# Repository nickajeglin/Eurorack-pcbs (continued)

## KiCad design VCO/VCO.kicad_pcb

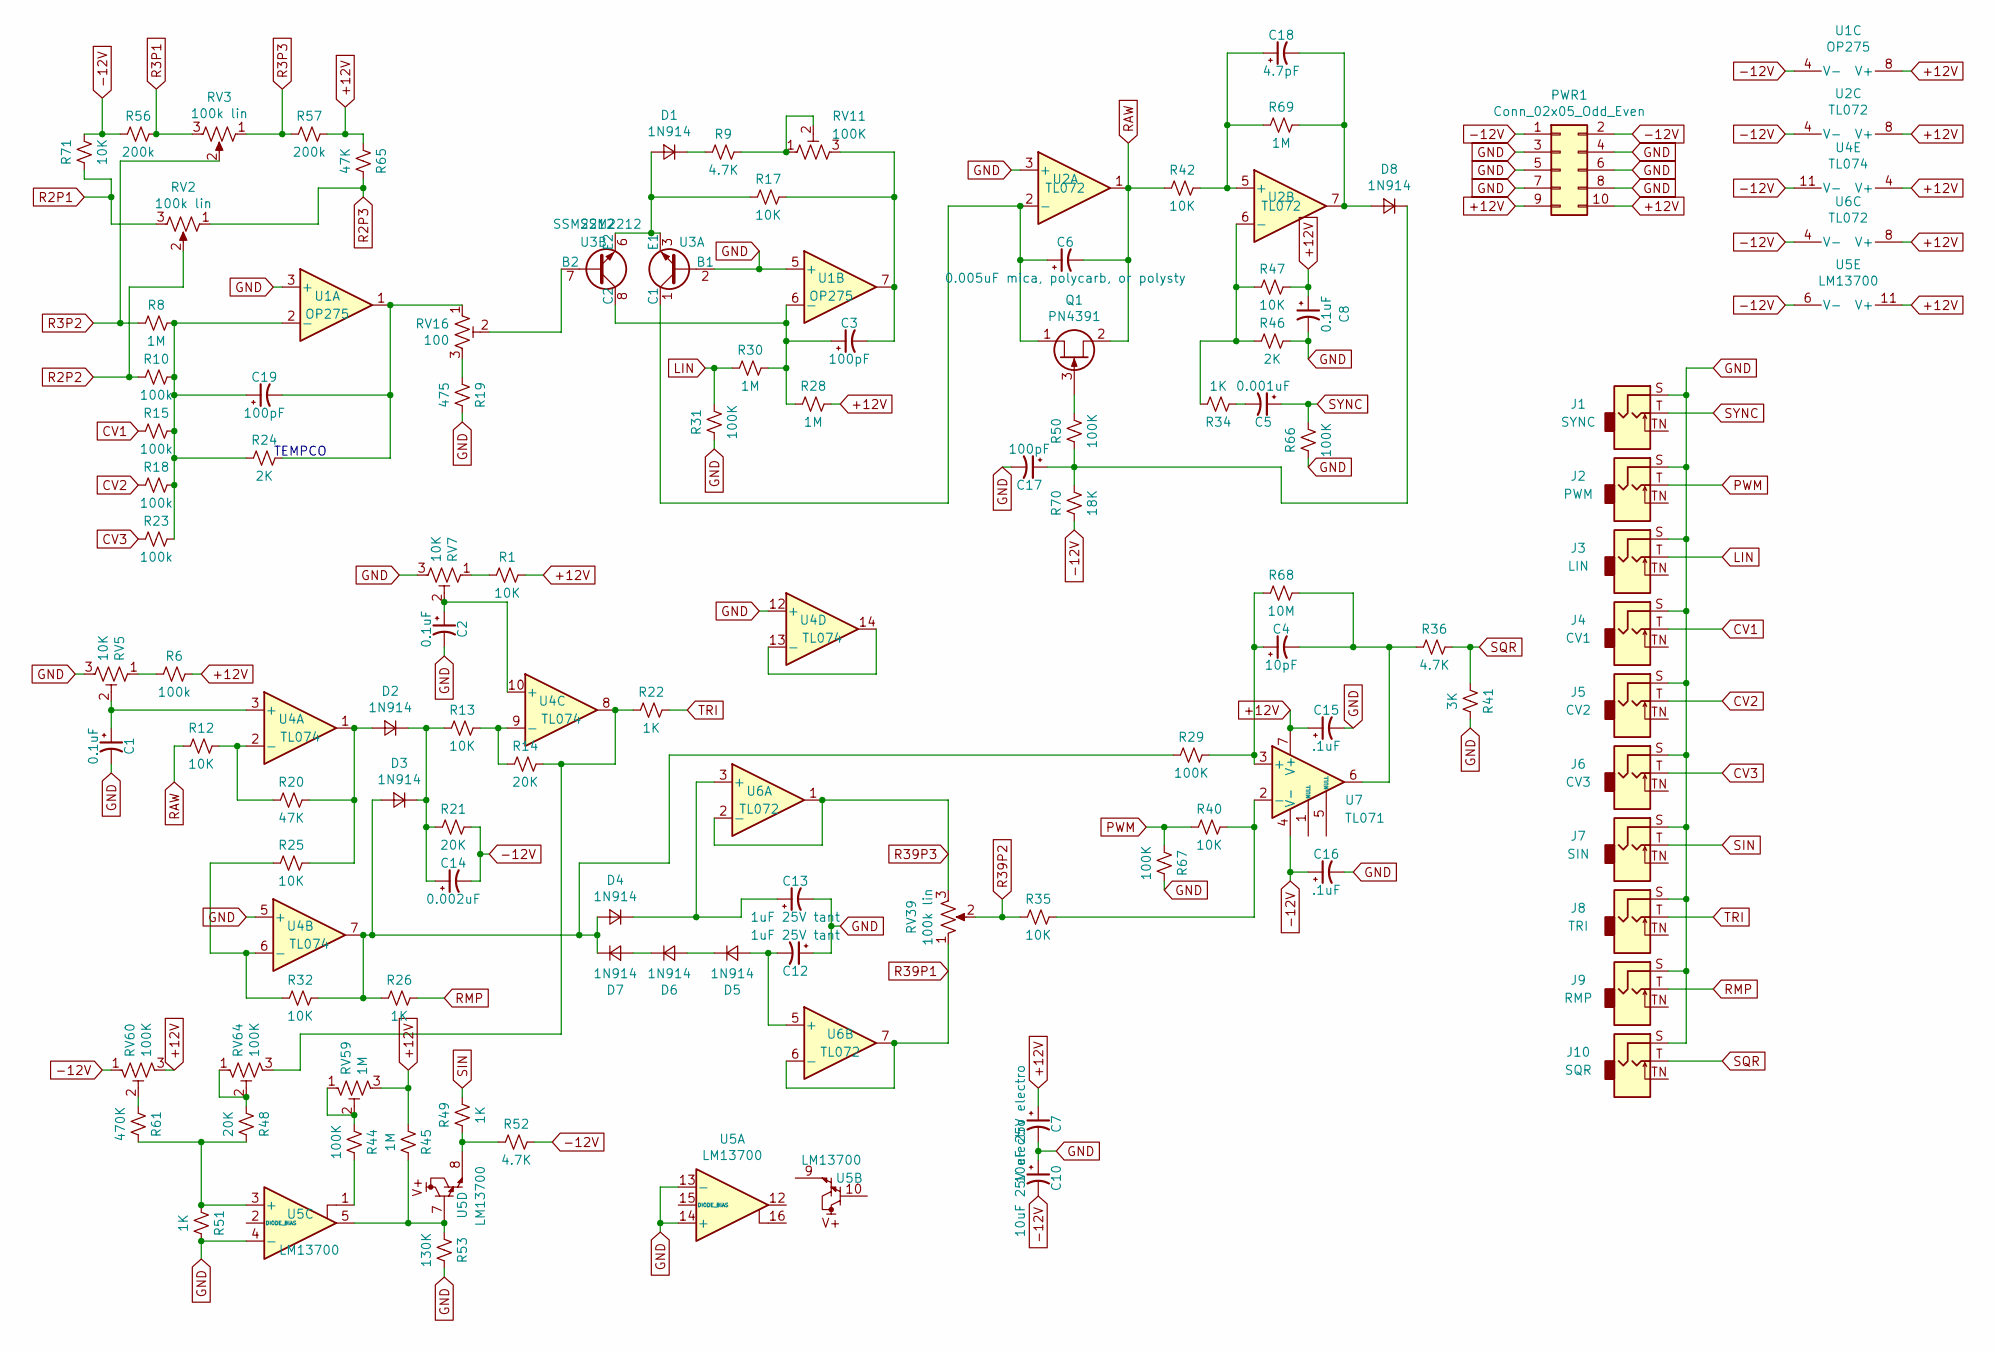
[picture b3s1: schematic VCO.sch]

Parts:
C1, C2, C8: 0.1uF; C_1206_3216Metric_Pad1.42x1.75mm_HandSolder
C3, C17, C19: 100pF; C_1206_3216Metric_Pad1.42x1.75mm_HandSolder
C4: 10pF; C_1206_3216Metric_Pad1.42x1.75mm_HandSolder
C5: 0.001uF; C_1206_3216Metric_Pad1.42x1.75mm_HandSolder
C6: 0.005uF mica, polycarb, or polysty; C_1206_3216Metric_Pad1.42x1.75mm_HandSolder
C7, C10: 10uF 25V electro; CP_Radial_D5.0mm_P2.50mm
C12, C13: 1uF 25V tant; C_1206_3216Metric_Pad1.42x1.75mm_HandSolder
C14: 0.002uF; C_1206_3216Metric_Pad1.42x1.75mm_HandSolder
C15, C16: .1uF; C_1206_3216Metric_Pad1.42x1.75mm_HandSolder
C18: 4.7pF; C_1206_3216Metric_Pad1.42x1.75mm_HandSolder
D1, D2, D3, D4, D5, D6, D7, D8: 1N914; D_1206_3216Metric_Pad1.42x1.75mm_HandSolder
J1: SYNC; 3.5mm_tip_switch_thonkiconn
J2: PWM; 3.5mm_tip_switch_thonkiconn
J3: LIN; 3.5mm_tip_switch_thonkiconn
J4: CV1; 3.5mm_tip_switch_thonkiconn
J5: CV2; 3.5mm_tip_switch_thonkiconn
J6: CV3; 3.5mm_tip_switch_thonkiconn
J7: SIN; 3.5mm_tip_switch_thonkiconn
J8: TRI; 3.5mm_tip_switch_thonkiconn
J9: RMP; 3.5mm_tip_switch_thonkiconn
J10: SQR; 3.5mm_tip_switch_thonkiconn
PWR1: Conn_02x05_Odd_Even; IDC-Header_2x05_P2.54mm_Vertical
Q1: PN4391; TO-92_Inline
R1, R12, R13, R17, R25, R32, R35, R40, R42, R47, R71: 10K; R_1206_3216Metric_Pad1.42x1.75mm_HandSolder
R6, R10, R15, R18, R23: 100k; R_1206_3216Metric_Pad1.42x1.75mm_HandSolder
R8, R28, R30, R45, R69: 1M; R_1206_3216Metric_Pad1.42x1.75mm_HandSolder
R9, R36, R52: 4.7K; R_1206_3216Metric_Pad1.42x1.75mm_HandSolder
R14, R21, R48: 20K; R_1206_3216Metric_Pad1.42x1.75mm_HandSolder
R19: 475; R_1206_3216Metric_Pad1.42x1.75mm_HandSolder
R20, R65: 47K; R_1206_3216Metric_Pad1.42x1.75mm_HandSolder
R22, R26, R34, R49, R51: 1K; R_1206_3216Metric_Pad1.42x1.75mm_HandSolder
R24, R46: 2K; R_1206_3216Metric_Pad1.42x1.75mm_HandSolder
R29, R31, R44, R50, R66, R67: 100K; R_1206_3216Metric_Pad1.42x1.75mm_HandSolder
R41: 3K; R_1206_3216Metric_Pad1.42x1.75mm_HandSolder
R53: 130K; R_1206_3216Metric_Pad1.42x1.75mm_HandSolder
R56, R57: 200k; R_1206_3216Metric_Pad1.42x1.75mm_HandSolder
R61: 470K; R_1206_3216Metric_Pad1.42x1.75mm_HandSolder
R68: 10M; R_1206_3216Metric_Pad1.42x1.75mm_HandSolder
R70: 18K; R_1206_3216Metric_Pad1.42x1.75mm_HandSolder
RV2, RV3, RV39: 100k lin; Potentiometer_Alps_RK09K_Single_Vertical
RV5, RV7: 10K; Potentiometer_Bourns_3296W_Vertical
RV11, RV60, RV64: 100K; Potentiometer_Bourns_3296W_Vertical
RV16: 100; Potentiometer_Bourns_3296W_Vertical
RV59: 1M; Potentiometer_Bourns_3296W_Vertical
U1: OP275; SOIC-8_3.9x4.9mm_P1.27mm
U2, U6: TL072; SOIC-8_3.9x4.9mm_P1.27mm
U3: SSM2212; SOIC-8_3.9x4.9mm_P1.27mm
U4: TL074; SOIC-14_3.9x8.7mm_P1.27mm
U5: LM13700; SOIC-16_3.9x9.9mm_P1.27mm
U7: TL071; SOIC-8_3.9x4.9mm_P1.27mm

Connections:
+12V: C7.1, C8.1, C15.1, PWR1.9, PWR1.10, R1.1, R6.1, R28.1, R45.2, R47.1, R57.1, R65.2, RV59.3, RV60.3, U1.8 (V+), U2.8 (V+), U4.4 (V+), U5.11 (V+), U6.8 (V+), U7.7 (V+)
-12V: C10.2, C14.2, C16.1, PWR1.1, PWR1.2, R21.1, R52.1, R56.2, R70.2, R71.1, RV60.1, U1.4 (V-), U2.4 (V-), U4.11 (V-), U5.6 (V-), U6.4 (V-), U7.4 (V-)
CV1: J4.T, R15.2
CV2: J5.T, R18.2
CV3: J6.T, R23.2
GND: C1.2, C2.2, C7.2, C8.2, C10.1, C12.1, C13.2, C15.2, C16.2, C17.2, J1.S, J2.S, J3.S, J4.S, J5.S, J6.S, J7.S, J8.S, J9.S, J10.S, PWR1.3, PWR1.4, PWR1.5, PWR1.6, PWR1.7, PWR1.8, R19.1, R31.2, R41.1, R46.1, R51.1, R53.1, R66.2, R67.1, RV5.3, RV7.3, U1.3 (+), U1.5 (+), U2.3 (+), U3.2 (B1), U4.5 (+), U4.12 (+), U5.4 (-), U5.13 (-), U5.14 (+)
LIN: J3.T, R30.2, R31.1
unnamed: C1.1, RV5.2, U4.3 (+)
unnamed: C2.1, RV7.2, U4.10 (+)
unnamed: C3.1, R28.2, R30.1, U1.6 (-), U3.8 (C2)
unnamed: C3.2, R17.1, RV11.3, U1.7
unnamed: C4.1, R29.1, R68.2, U7.3 (+)
unnamed: C4.2, R36.2, R68.1, U7.6
unnamed: C5.2, R34.2
unnamed: C6.1, Q1.1 (D), U2.2 (-), U3.1 (C1)
unnamed: C12.2, D5.2 (A), U6.5 (+)
unnamed: C13.1, D4.1 (K), U6.3 (+)
unnamed: C14.1, D2.1 (K), D3.1 (K), R13.2, R21.2
unnamed: C17.1, D8.1 (K), R50.2, R70.1
unnamed: C18.1, R42.1, R69.2, U2.5 (+)
unnamed: C18.2, D8.2 (A), R69.1, U2.7
unnamed: C19.1, R8.1, R10.1, R15.1, R18.1, R23.1, R24.2, U1.2 (-)
unnamed: C19.2, R24.1, RV16.1, U1.1
unnamed: D1.1 (K), R9.2
unnamed: D1.2 (A), R17.2, U3.3 (E1), U3.6 (E2)
unnamed: D2.2 (A), R20.1, R25.1, U4.1
unnamed: D3.2 (A), D4.2 (A), D7.1 (K), R26.2, R29.2, R32.1, U4.7
unnamed: D5.1 (K), D6.2 (A)
unnamed: D6.1 (K), D7.2 (A)
unnamed: Q1.3 (G), R50.1
unnamed: R1.2, RV7.1
unnamed: R6.2, RV5.1
unnamed: R9.1, RV11.1, RV11.2
unnamed: R12.1, R20.2, U4.2 (-)
unnamed: R13.1, R14.2, U4.9 (-)
unnamed: R14.1, R22.2, RV64.3, U4.8
unnamed: R19.2, RV16.3
unnamed: R25.2, R32.2, U4.6 (-)
unnamed: R34.1, R46.2, R47.2, U2.6 (-)
unnamed: R35.1, R40.1, U7.2 (-)
unnamed: R44.1, U5.1
unnamed: R44.2, RV59.1, RV59.2
unnamed: R45.1, R53.2, U5.5, U5.7
unnamed: R48.1, R51.2, R61.1, U5.3 (+)
unnamed: R48.2, RV64.1, RV64.2
unnamed: R49.2, R52.2, U5.8
unnamed: R61.2, RV60.2
unnamed: RV16.2, U3.7 (B2)
unnamed: U4.13 (-), U4.14
PWM: J2.T, R40.2, R67.2
R2P1: R71.2, RV2.3
R2P2: R10.2, RV2.2
R2P3: R65.1, RV2.1
R3P1: R56.1, RV3.3
R3P2: R8.2, RV3.2
R3P3: R57.2, RV3.1
R39P1: RV39.1, U6.6 (-), U6.7
R39P2: R35.2, RV39.2
R39P3: RV39.3, U6.1, U6.2 (-)
RAW: C6.2, Q1.2 (S), R12.2, R42.2, U2.1
RMP: J9.T, R26.1
SIN: J7.T, R49.1
SQR: J10.T, R36.1, R41.2
SYNC: C5.1, J1.T, R66.1
TRI: J8.T, R22.1

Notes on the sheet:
TEMPCO

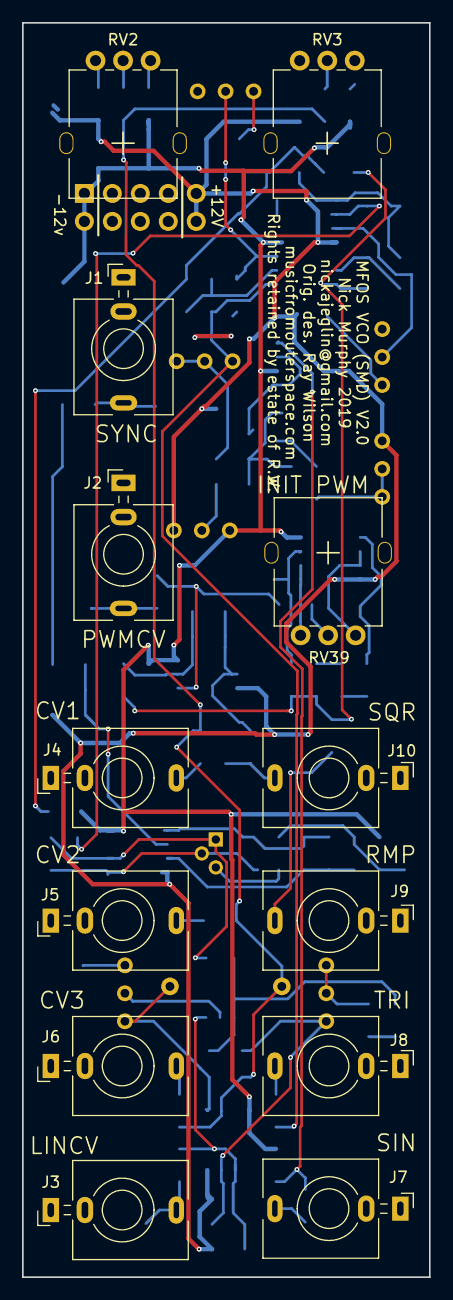
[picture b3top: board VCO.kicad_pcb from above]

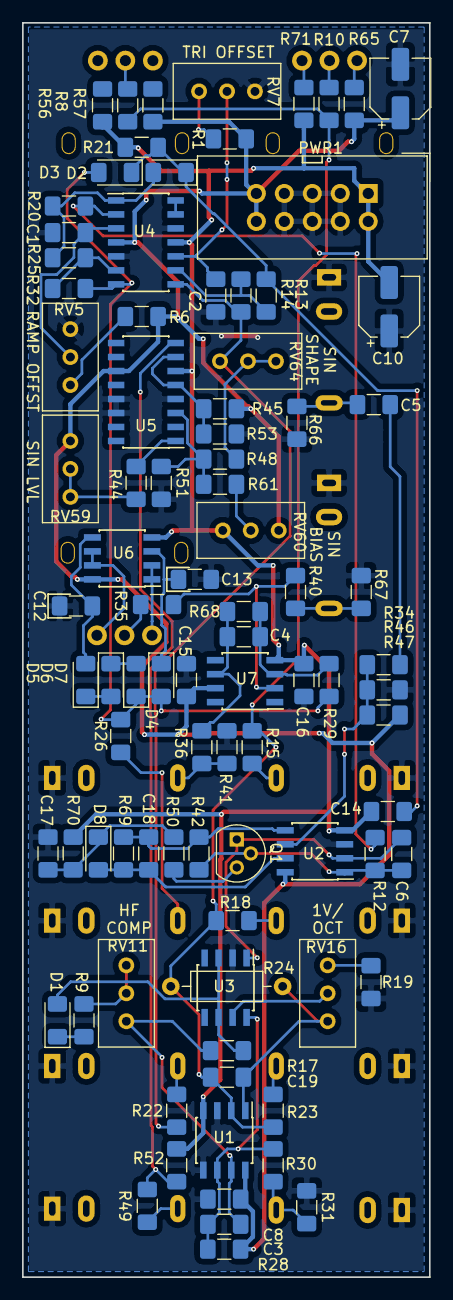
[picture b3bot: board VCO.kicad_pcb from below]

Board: 2 copper layers, 37.0 x 113.9 mm, 104 parts (91 on the bottom side), 65 nets.

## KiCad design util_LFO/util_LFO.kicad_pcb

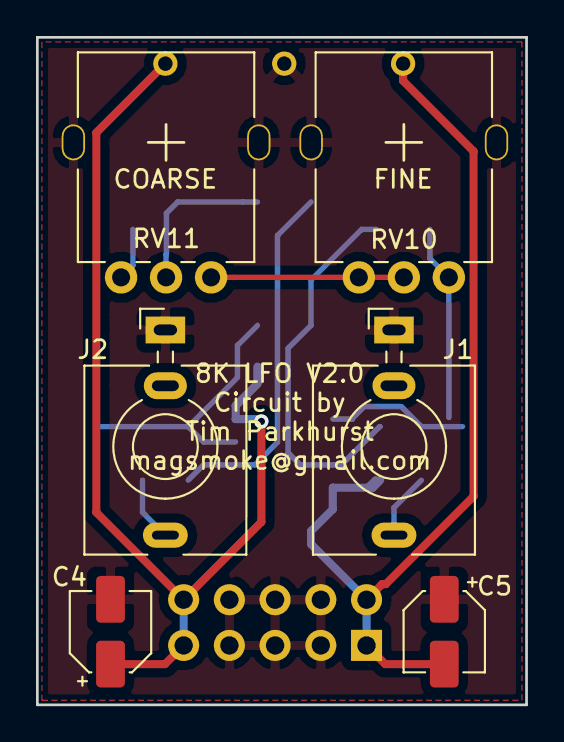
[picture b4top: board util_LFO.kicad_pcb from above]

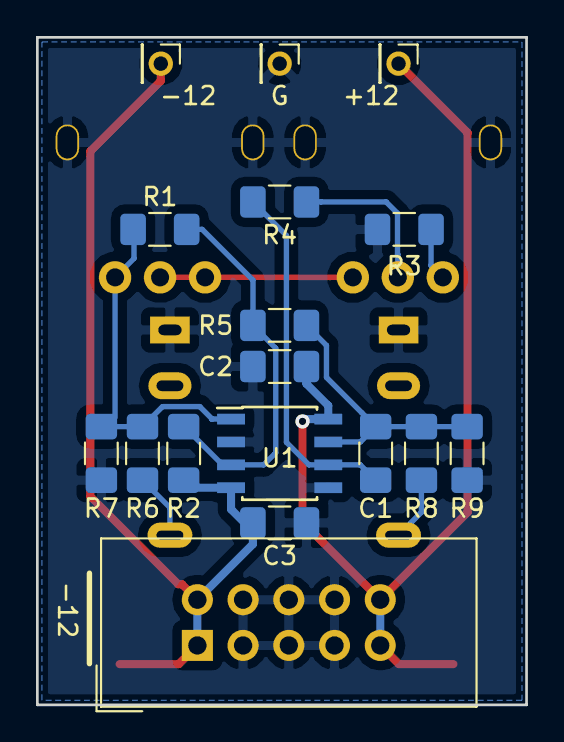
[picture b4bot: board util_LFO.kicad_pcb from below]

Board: 2 copper layers, 27.2 x 37.1 mm, 23 parts (17 on the bottom side), 12 nets.

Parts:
C1: 3300pF; C_1206_3216Metric_Pad1.42x1.75mm_HandSolder
C2, C3: 0.1uF; C_1206_3216Metric_Pad1.42x1.75mm_HandSolder
C4, C5: 10uF; CP_Elec_4x5.4
J1: SQR; 3.5mm_tip_switch_thonkiconn
J2: TRI; 3.5mm_tip_switch_thonkiconn
J3: Conn_02x05_Odd_Even; IDC-Header_2x05_P2.54mm_Vertical
J4: +12; PinHeader_1x01_P2.00mm_Vertical
J5: GND; PinHeader_1x01_P2.00mm_Vertical
J6: -12; PinHeader_1x01_P2.00mm_Vertical
R1: 200K; R_1206_3216Metric_Pad1.42x1.75mm_HandSolder
R2: 5M; R_1206_3216Metric_Pad1.42x1.75mm_HandSolder
R3: 220R; R_1206_3216Metric_Pad1.42x1.75mm_HandSolder
R4: 1M; R_1206_3216Metric_Pad1.42x1.75mm_HandSolder
R5: 100K; R_1206_3216Metric_Pad1.42x1.75mm_HandSolder
R6, R9: 10K; R_1206_3216Metric_Pad1.42x1.75mm_HandSolder
R7: 4.7K; R_1206_3216Metric_Pad1.42x1.75mm_HandSolder
R8: 2K; R_1206_3216Metric_Pad1.42x1.75mm_HandSolder
RV10, RV11: A1M; Potentiometer_Thonk_Alpha_9mm_Vertical
U1: TL072; SOIC-8_3.9x4.9mm_P1.27mm

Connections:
+12v: C2.1, C4.1, J3.9, J3.10, J4.1, U1.8
-12V: C3.2, C5.2, J3.1, J3.2, J6.1, R2.2, U1.4
GND: C2.2, C3.1, C4.2, C5.1, J1.S, J2.S, J3.3, J3.4, J3.5, J3.6, J3.7, J3.8, J5.1, R3.1, R7.2, R9.2, U1.2, U1.5
unnamed: C1.1, R4.1, U1.6
unnamed: C1.2, R5.1, R8.1, R9.1, U1.7
unnamed: J1.T, R6.2
unnamed: J2.T, R8.2
unnamed: R1.1, R6.1, R7.1, RV10.1, U1.1
unnamed: R1.2, R2.1, R5.2, U1.3
unnamed: R3.2, RV11.3
unnamed: R4.2, RV11.2
unnamed: RV10.2, RV10.3, RV11.1

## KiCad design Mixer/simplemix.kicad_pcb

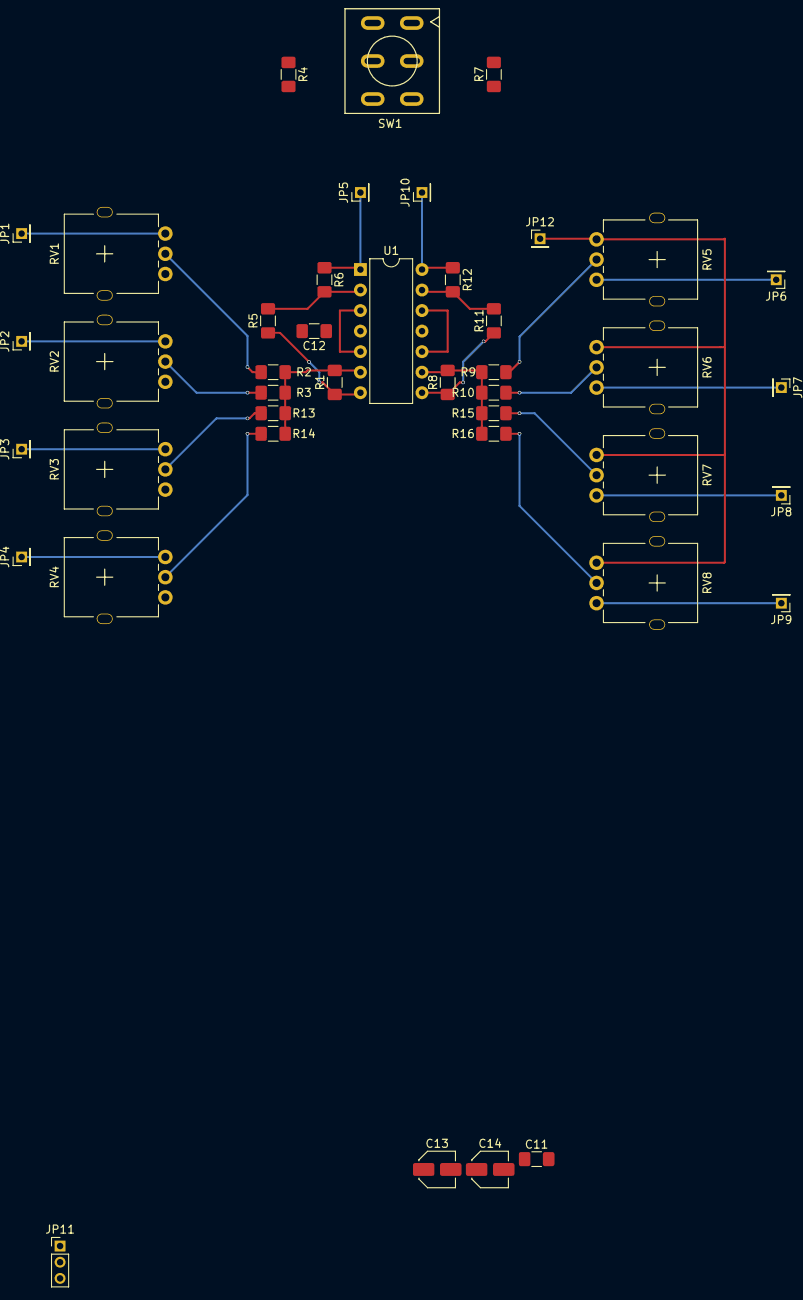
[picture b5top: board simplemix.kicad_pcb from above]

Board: 2 copper layers, 42 parts (0 on the bottom side), 29 nets.

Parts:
C11, C12: 0.1uF; C_1206_3216Metric_Pad1.42x1.75mm_HandSolder
C13, C14: 10uF; C_Elec_4x5.4
JP1: IN1; PinHeader_1x01_P2.00mm_Vertical
JP2: IN2; PinHeader_1x01_P2.00mm_Vertical
JP3: IN3; PinHeader_1x01_P2.00mm_Vertical
JP4: IN4; PinHeader_1x01_P2.00mm_Vertical
JP5: OUT1; PinHeader_1x01_P2.00mm_Vertical
JP6: IN5; PinHeader_1x01_P2.00mm_Vertical
JP7: IN6; PinHeader_1x01_P2.00mm_Vertical
JP8: IN7; PinHeader_1x01_P2.00mm_Vertical
JP9: IN8; PinHeader_1x01_P2.00mm_Vertical
JP10: OUT2; PinHeader_1x01_P2.00mm_Vertical
JP11: PWR CHAIN; PinHeader_1x03_P2.00mm_Vertical
JP12: GND; PinHeader_1x01_P2.00mm_Vertical
R1, R4, R5, R6, R7, R8, R11, R12: 100K; R_1206_3216Metric_Pad1.42x1.75mm_HandSolder
R2, R3, R9, R10, R13, R14, R15, R16: 33K; R_1206_3216Metric_Pad1.42x1.75mm_HandSolder
RV1, RV2, RV3, RV4, RV5, RV6, RV7, RV8: 100K; Potentiometer_Thonk_Alpha_9mm_Vertical
SW1: CONFIG; toggle_switch_mini_DPDT
U1: TL074; DIP-14_W7.62mm

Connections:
+12V: C12.1, C14.1, JP11.3, U1.4
-12V: C11.1, C13.2, JP11.1, U1.11
GND: C11.2, C12.2, C13.1, C14.2, JP11.2, JP12.1, RV1.3, RV2.3, RV3.3, RV4.3, RV5.3, RV6.3, RV7.3, RV8.3, U1.3, U1.5, U1.10, U1.12
unnamed: JP1.1, RV1.1
unnamed: JP2.1, RV2.1
unnamed: JP3.1, RV3.1
unnamed: JP4.1, RV4.1
unnamed: JP5.1, R6.1, U1.1
unnamed: JP6.1, RV5.1
unnamed: JP7.1, RV6.1
unnamed: JP8.1, RV7.1
unnamed: JP9.1, RV8.1
unnamed: JP10.1, R12.1, U1.14
unnamed: R1.1, R5.1, SW1.2, U1.7
unnamed: R1.2, R2.1, R3.1, R13.1, R14.1, U1.6
unnamed: R2.2, RV1.2
unnamed: R3.2, RV2.2
unnamed: R4.1, SW1.5
unnamed: R4.2, R5.2, R6.2, U1.2
unnamed: R7.2, SW1.1
unnamed: R9.2, RV5.2
unnamed: R8.2, R9.1, R10.1, R15.1, R16.1, U1.9
unnamed: R10.2, RV6.2
unnamed: R8.1, R11.1, SW1.4, U1.8
unnamed: R7.1, R11.2, R12.2, U1.13
unnamed: R13.2, RV3.2
unnamed: R14.2, RV4.2
unnamed: R15.2, RV7.2
unnamed: R16.2, RV8.2

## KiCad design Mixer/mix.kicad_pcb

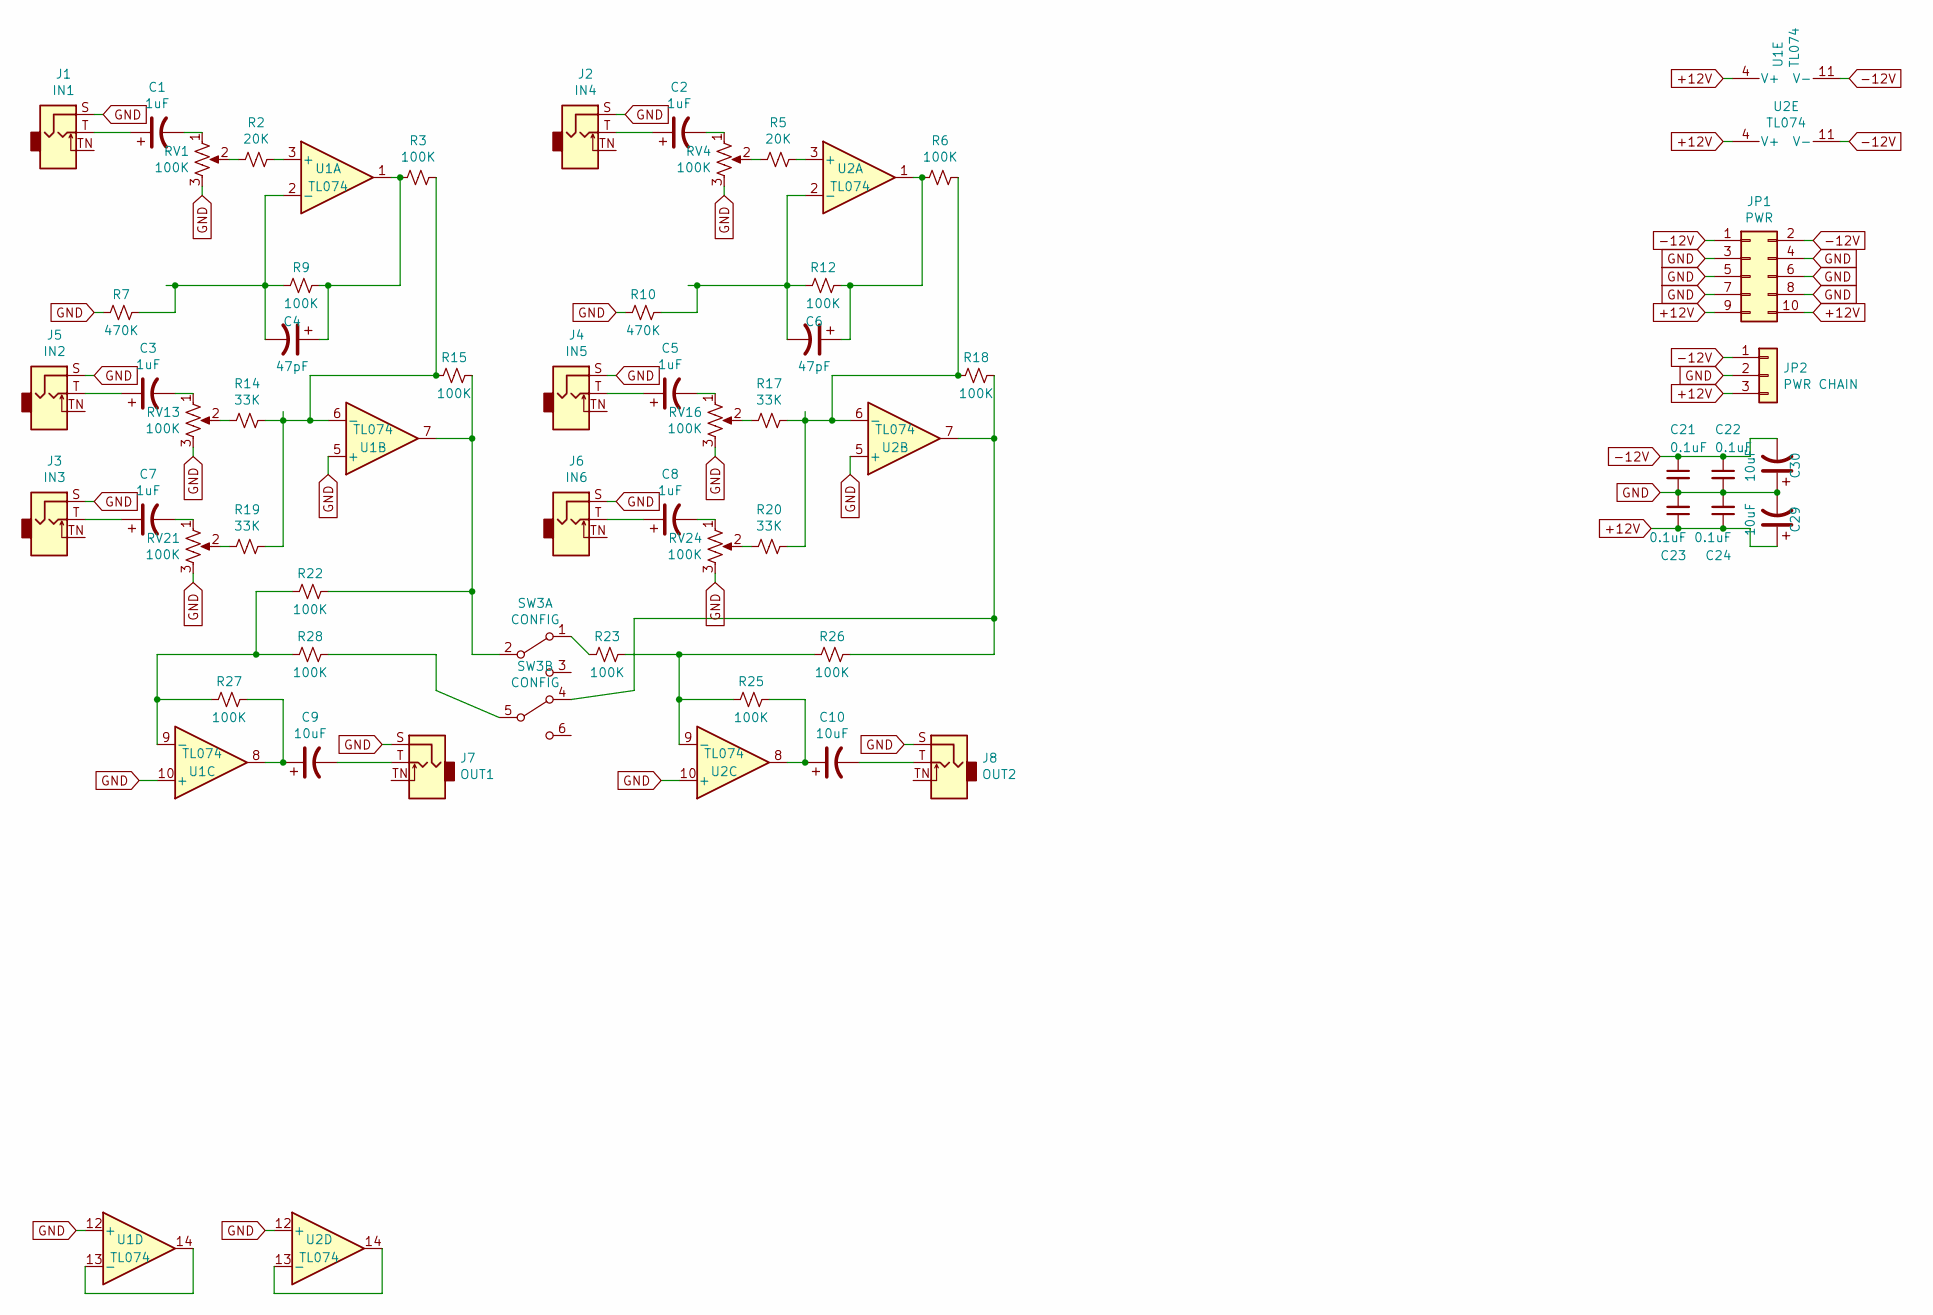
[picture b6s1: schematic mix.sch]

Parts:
C1, C2, C3, C5, C7, C8: 1uF; CP_Elec_6.3x5.4
C4, C6: 47pF; C_1206_3216Metric_Pad1.42x1.75mm_HandSolder
C9, C10, C29, C30: 10uF; CP_Elec_6.3x5.4
C21, C22, C23, C24: 0.1uF; C_1206_3216Metric_Pad1.42x1.75mm_HandSolder
J1: IN1; 3.5mm_tip_switch_thonkiconn
J2: IN4; 3.5mm_tip_switch_thonkiconn
J3: IN3; 3.5mm_tip_switch_thonkiconn
J4: IN5; 3.5mm_tip_switch_thonkiconn
J5: IN2; 3.5mm_tip_switch_thonkiconn
J6: IN6; 3.5mm_tip_switch_thonkiconn
J7: OUT1; 3.5mm_tip_switch_thonkiconn
J8: OUT2; 3.5mm_tip_switch_thonkiconn
JP1: PWR; IDC-Header_2x05_P2.54mm_Vertical
JP2: PWR CHAIN; PinHeader_1x03_P2.54mm_Vertical
R2, R5: 20K; R_1206_3216Metric_Pad1.42x1.75mm_HandSolder
R3, R6, R9, R12, R15, R18, R22, R23, R25, R26, R27, R28: 100K; R_1206_3216Metric_Pad1.42x1.75mm_HandSolder
R7, R10: 470K; R_1206_3216Metric_Pad1.42x1.75mm_HandSolder
R14, R17, R19, R20: 33K; R_1206_3216Metric_Pad1.42x1.75mm_HandSolder
RV1, RV4, RV13, RV16, RV21, RV24: 100K; Potentiometer_Thonk_Alpha_9mm_Vertical
SW3: CONFIG; toggle_switch_mini_DPDT
U1, U2: TL074; SOIC-14_3.9x8.7mm_P1.27mm

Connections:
+12V: C23.1, C24.1, C29.1, JP1.9, JP1.10, JP2.3, U1.4 (V+), U2.4 (V+)
-12V: C21.1, C22.1, C30.2, JP1.1, JP1.2, JP2.1, U1.11 (V-), U2.11 (V-)
GND: C21.2, C22.2, C23.2, C24.2, C29.2, C30.1, J1.S, J2.S, J3.S, J4.S, J5.S, J6.S, J7.S, J8.S, JP1.3, JP1.4, JP1.5, JP1.6, JP1.7, JP1.8, JP2.2, R7.2, R10.2, RV1.3, RV4.3, RV13.3, RV16.3, RV21.3, RV24.3, U1.5 (+), U1.10 (+), U1.12 (+), U2.5 (+), U2.10 (+), U2.12 (+)
unnamed: C1.1, J1.T
unnamed: C1.2, RV1.1
unnamed: C2.1, J2.T
unnamed: C2.2, RV4.1
unnamed: C3.1, J5.T
unnamed: C3.2, RV13.1
unnamed: C4.1, R3.2, R9.1, U1.1
unnamed: C5.1, J4.T
unnamed: C5.2, RV16.1
unnamed: C6.1, R6.2, R12.1, U2.1
unnamed: C7.1, J3.T
unnamed: C7.2, RV21.1
unnamed: C8.1, J6.T
unnamed: C8.2, RV24.1
unnamed: C9.1, R27.1, U1.8
unnamed: C9.2, J7.T
unnamed: C10.1, R25.1, U2.8
unnamed: C10.2, J8.T
unnamed: R2.1, U1.3 (+)
unnamed: R2.2, RV1.2
unnamed: R5.1, U2.3 (+)
unnamed: R5.2, RV4.2
unnamed: R3.1, R14.1, R15.2, R19.1, U1.6 (-)
unnamed: R14.2, RV13.2
unnamed: R15.1, R22.1, SW3.2 (B), U1.7
unnamed: R6.1, R17.1, R18.2, R20.1, U2.6 (-)
unnamed: R17.2, RV16.2
unnamed: R18.1, R26.1, SW3.4 (A), U2.7
unnamed: R19.2, RV21.2
unnamed: R20.2, RV24.2
unnamed: R22.2, R27.2, R28.2, U1.9 (-)
unnamed: R23.1, R25.2, R26.2, U2.9 (-)
unnamed: R23.2, SW3.1 (A)
unnamed: R28.1, SW3.5 (B)
unnamed: U1.13 (-), U1.14
unnamed: U2.13 (-), U2.14

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
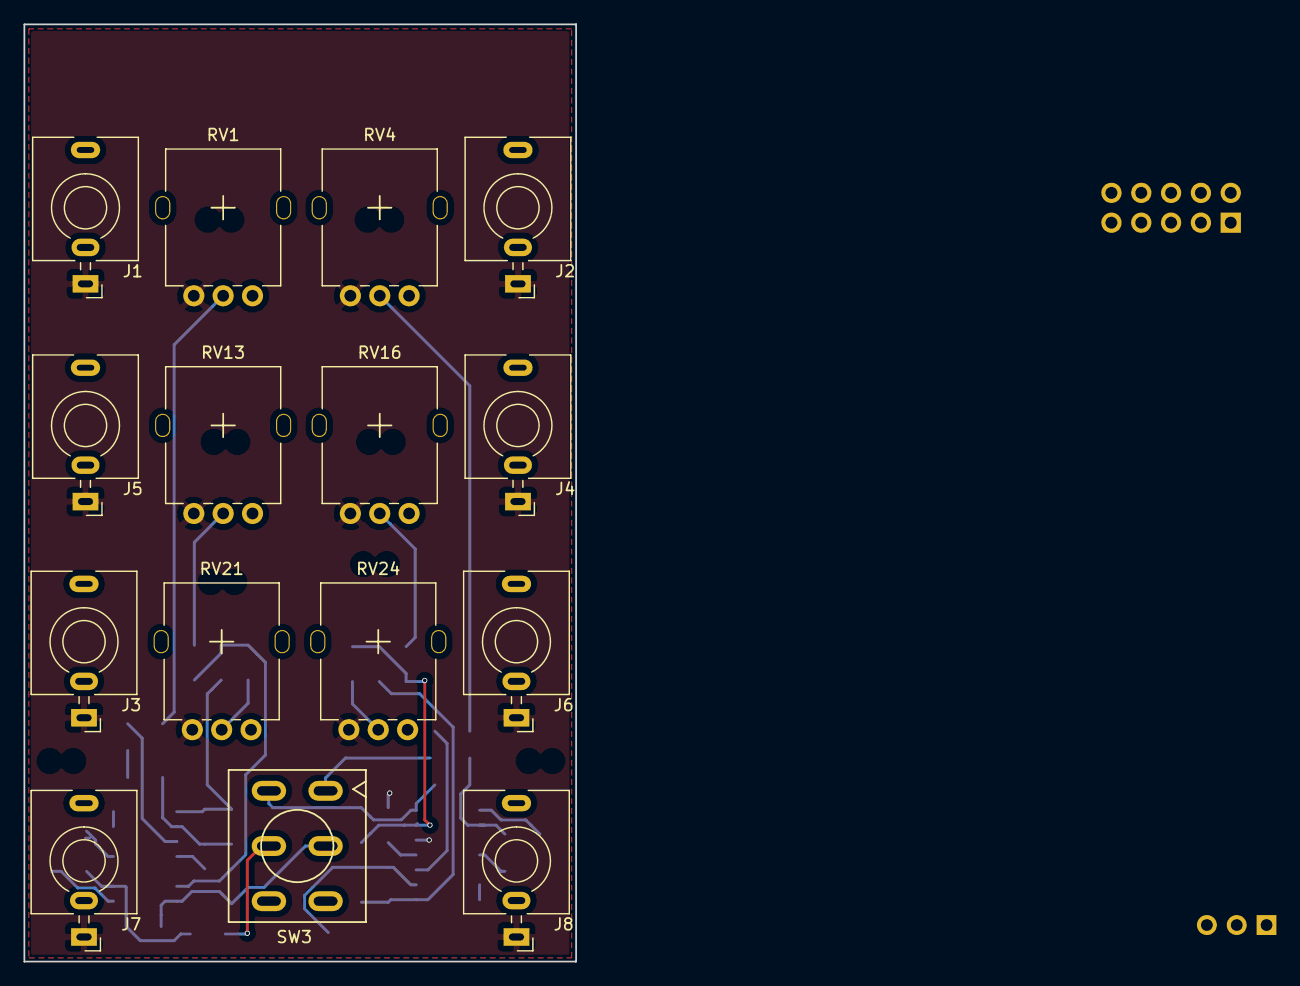
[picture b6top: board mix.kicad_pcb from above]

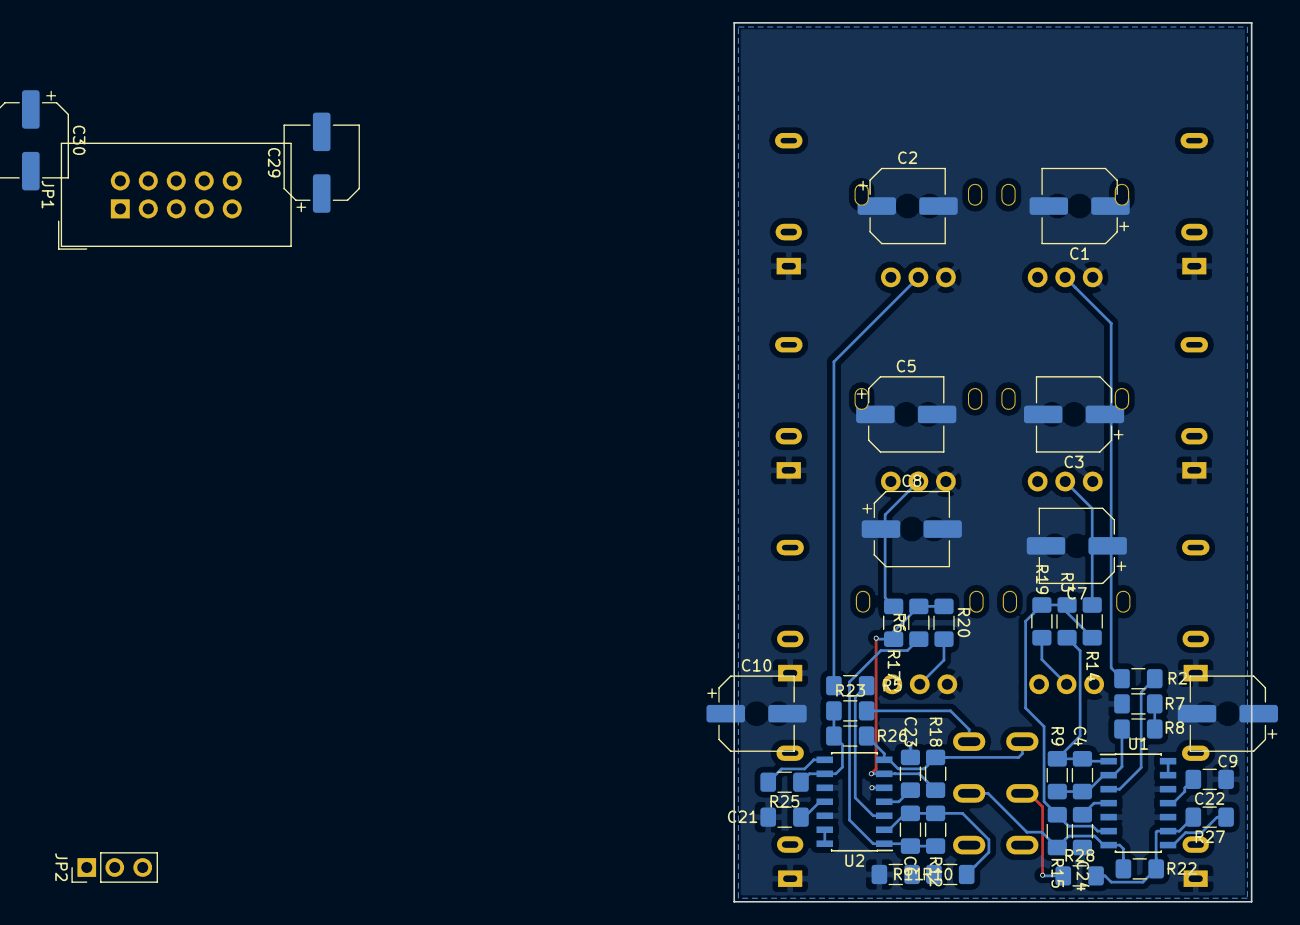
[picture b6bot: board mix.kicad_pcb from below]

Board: 2 copper layers, 47.0 x 79.8 mm, 57 parts (42 on the bottom side), 43 nets.

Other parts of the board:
R8, R11: 2K; R_1206_3216Metric_Pad1.42x1.75mm_HandSolder

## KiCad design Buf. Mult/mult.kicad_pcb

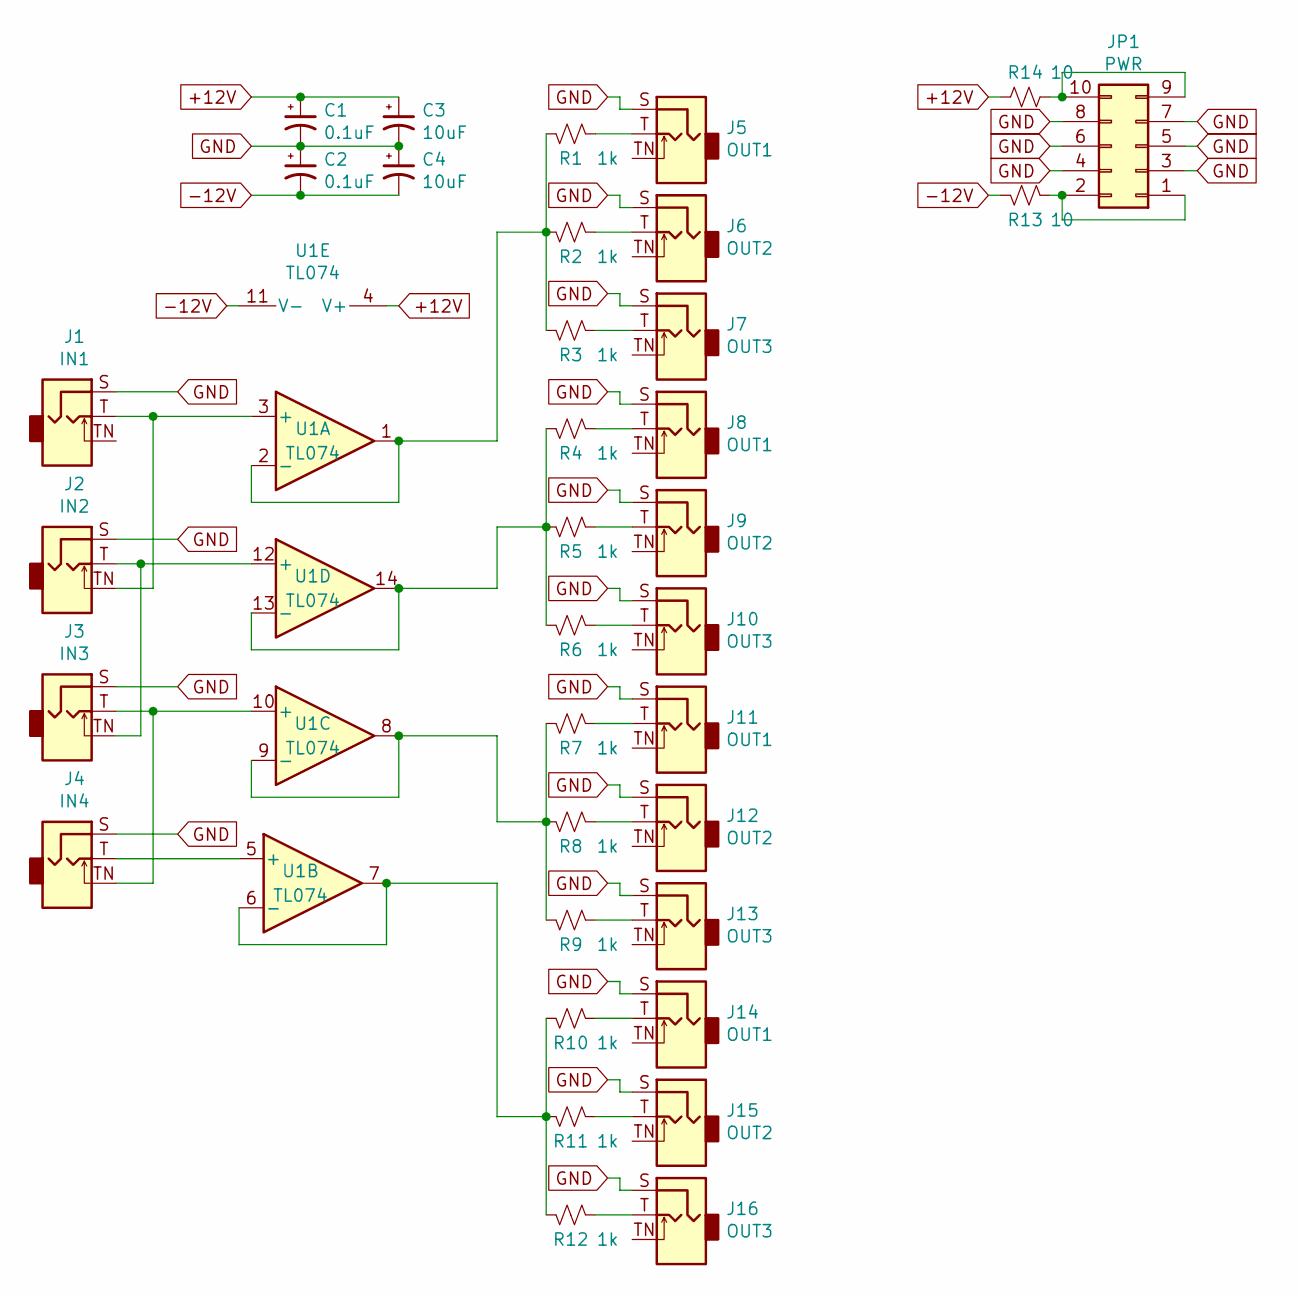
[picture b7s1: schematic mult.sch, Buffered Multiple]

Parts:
C1, C2: 0.1uF; C_Disc_D3.0mm_W1.6mm_P2.50mm
C3, C4: 10uF; CP_Radial_D5.0mm_P2.50mm
J1: IN1; 3.5mm_tip_switch_thonkiconn
J2: IN2; 3.5mm_tip_switch_thonkiconn
J3: IN3; 3.5mm_tip_switch_thonkiconn
J4: IN4; 3.5mm_tip_switch_thonkiconn
J5, J8, J11, J14: OUT1; 3.5mm_tip_switch_thonkiconn
J6, J9, J12, J15: OUT2; 3.5mm_tip_switch_thonkiconn
J7, J10, J13, J16: OUT3; 3.5mm_tip_switch_thonkiconn
JP1: PWR; IDC-Header_2x05_P2.54mm_Vertical
R1, R2, R3, R4, R5, R6, R7, R8, R9, R10, R11, R12: 1k; R_Axial_DIN0207_L6.3mm_D2.5mm_P7.62mm_Horizontal
R13, R14: 10; R_Axial_DIN0207_L6.3mm_D2.5mm_P7.62mm_Horizontal
U1: TL074; DIP-14_W7.62mm

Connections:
+12V: C1.1, C3.1, R14.2, U1.4 (V+)
-12V: C2.2, C4.2, R13.2, U1.11 (V-)
GND: C1.2, C2.1, C3.2, C4.1, J1.S, J2.S, J3.S, J4.S, J5.S, J6.S, J7.S, J8.S, J9.S, J10.S, J11.S, J12.S, J13.S, J14.S, J15.S, J16.S, JP1.3, JP1.4, JP1.5, JP1.6, JP1.7, JP1.8
unnamed: J1.T, J2.TN, U1.3 (+)
unnamed: J2.T, J3.TN, U1.12 (+)
unnamed: J3.T, J4.TN, U1.10 (+)
unnamed: J4.T, U1.5 (+)
unnamed: J5.T, R1.1
unnamed: J6.T, R2.1
unnamed: J7.T, R3.1
unnamed: J8.T, R4.1
unnamed: J9.T, R5.1
unnamed: J10.T, R6.1
unnamed: J11.T, R7.1
unnamed: J12.T, R8.1
unnamed: J13.T, R9.1
unnamed: J14.T, R10.1
unnamed: J15.T, R11.1
unnamed: J16.T, R12.1
unnamed: JP1.1, JP1.2, R13.1
unnamed: JP1.9, JP1.10, R14.1
unnamed: R1.2, R2.2, R3.2, U1.1, U1.2 (-)
unnamed: R4.2, R5.2, R6.2, U1.13 (-), U1.14
unnamed: R7.2, R8.2, R9.2, U1.8, U1.9 (-)
unnamed: R10.2, R11.2, R12.2, U1.6 (-), U1.7

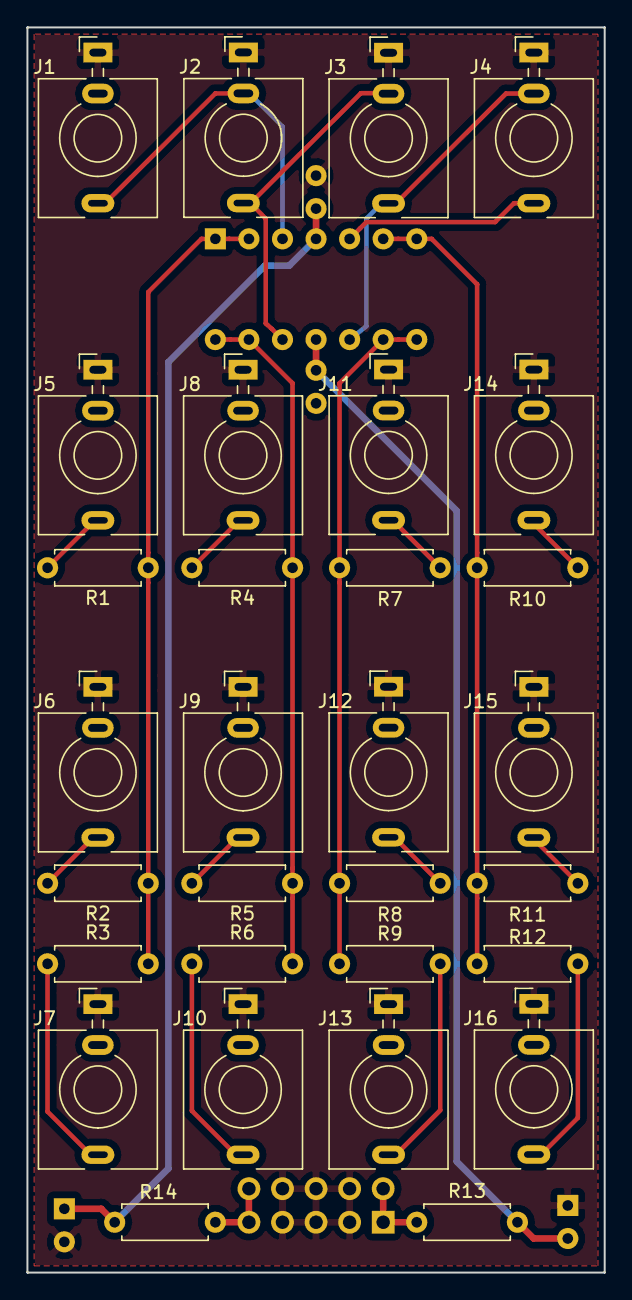
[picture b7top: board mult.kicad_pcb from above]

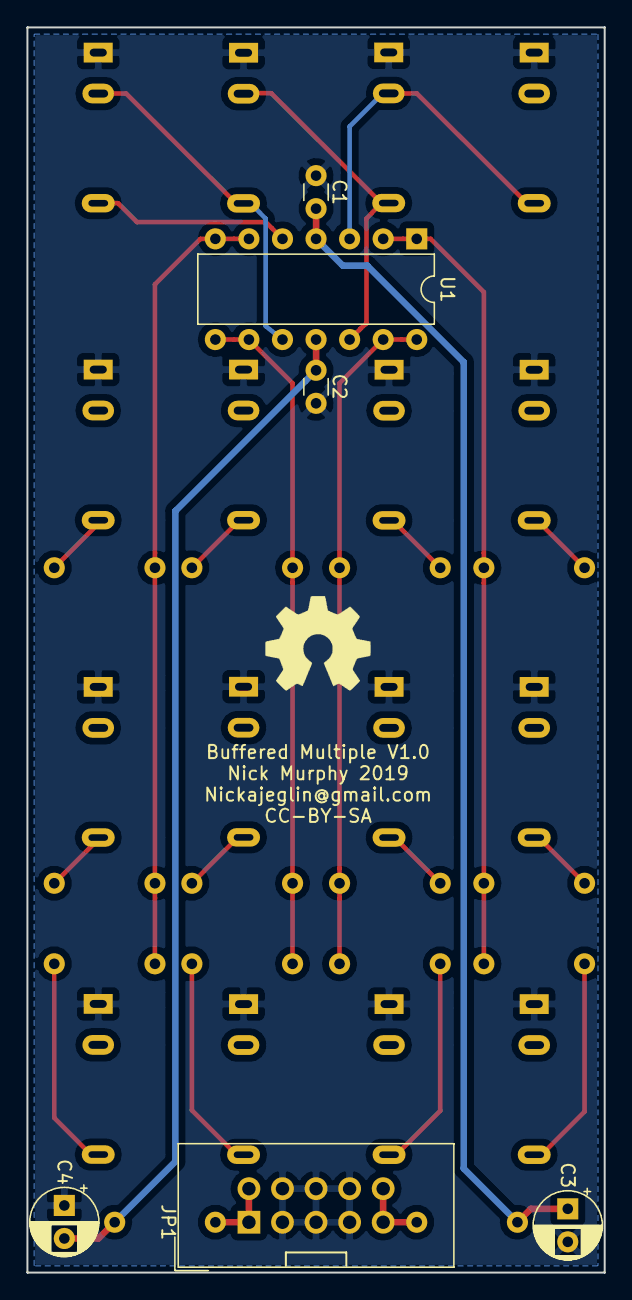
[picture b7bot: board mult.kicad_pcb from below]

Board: 2 copper layers, 43.7 x 94.2 mm, 36 parts (6 on the bottom side), 25 nets.
